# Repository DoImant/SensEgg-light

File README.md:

# SensEgg-Light

This is a circuit board layout for a weather sensor. A BME280 is used to measure temperature, humidity and air pressure. In addition, an NTC ( B+B Sensors TS-NTC-103) is used for temperature measurement, the accuracy of which is significantly better than that of the BME280. The recorded data is sent to a receiver by radio (nrf24 module). 

Power is supplied via a CR2032 3V coin cell. The name comes from the fact that the circuit board fits into a kinder surprise (egg).

The creator of this PCB is @Spaghetticode from arduinoforum.de. I have only implemented his design in KiCad.

## More about the Sensegg-Ligth (in german) 

[https://www.arduinoforum.de/arduino-Thread-SensEgg-light-FunkSensor-ATtiny814-nRF24-BME280-NTC](https://www.arduinoforum.de/arduino-Thread-SensEgg-light-FunkSensor-ATtiny814-nRF24-BME280-NTC)

[SensEgg Firmware](https://github.com/DoImant/Arduino-SensEgg-Light)

## Circuit diagram as PDF file

[Circuit diagram](/SensEgg.pdf)

## The PCB

[Aisler](https://aisler.net/p/TQVCAVJF)

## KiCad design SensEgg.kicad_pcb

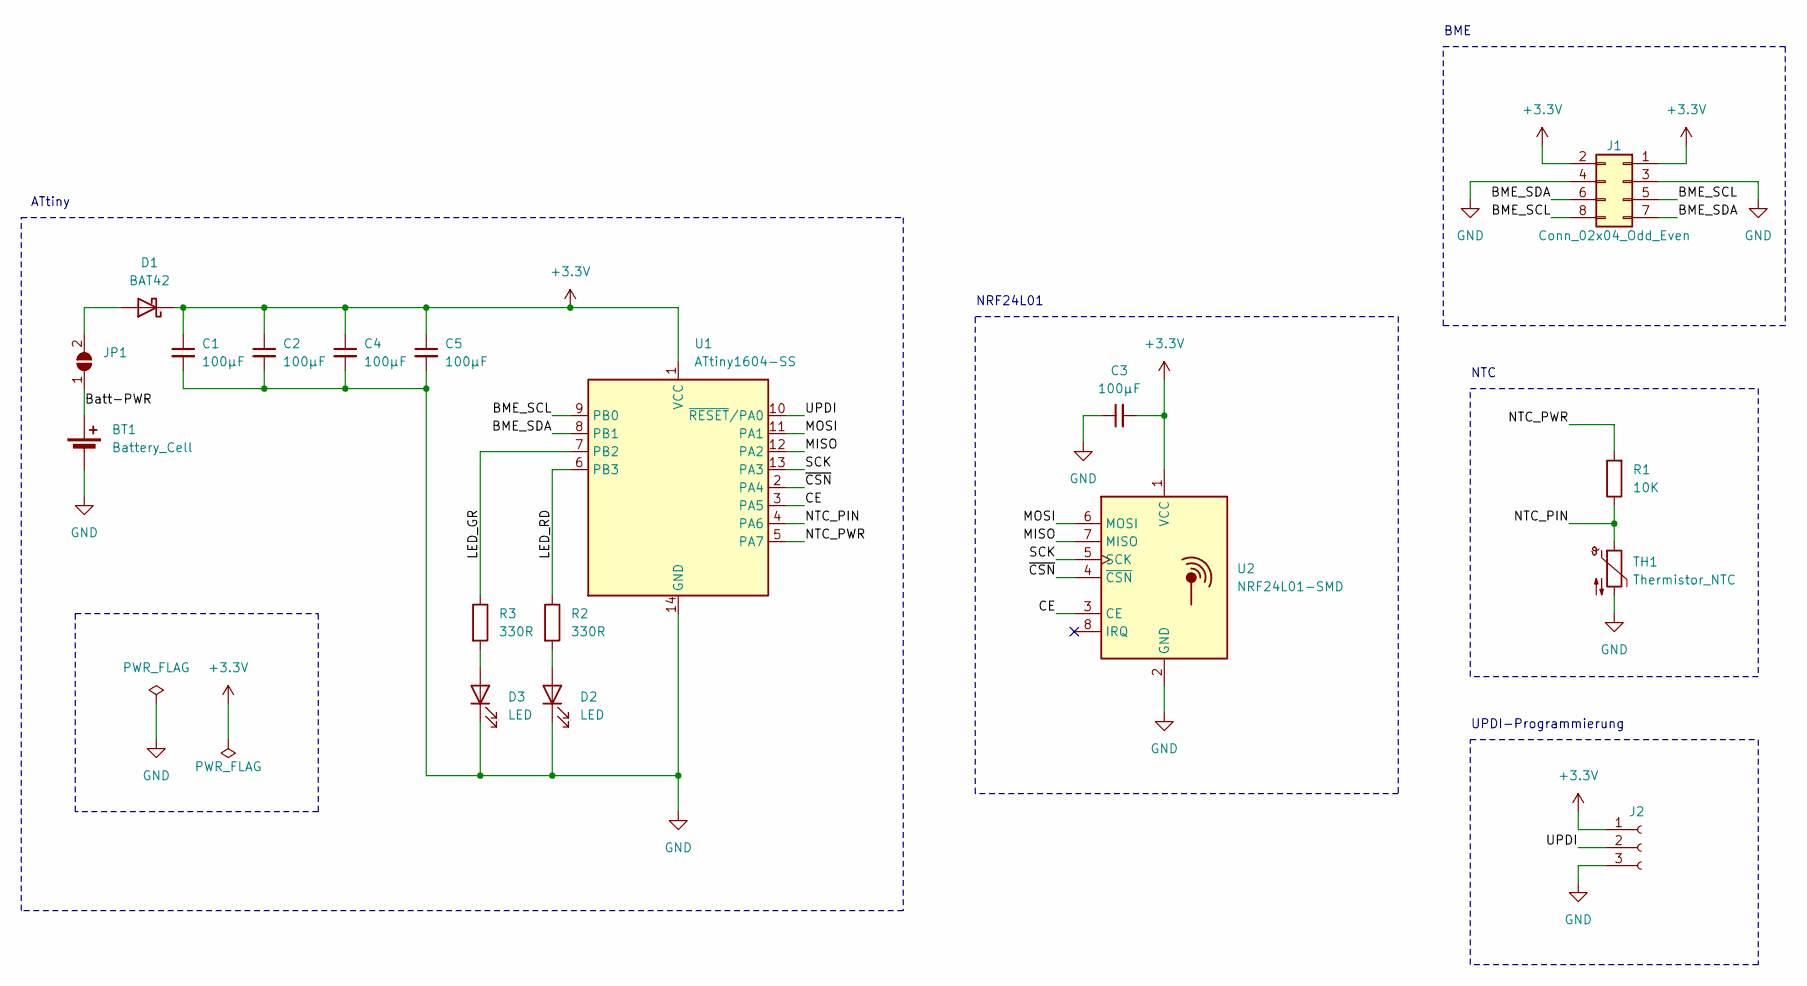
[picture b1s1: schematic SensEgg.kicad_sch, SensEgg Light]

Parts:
BT1: Battery_Cell; China-CR2032
C1, C2, C3, C4, C5: 100µF; C_1206_3216Metric_Pad1.33x1.80mm_HandSolder
D1: BAT42; D_1206_3216Metric_Pad1.42x1.75mm_HandSolder
D2, D3: LED; LED_1206_3216Metric_Pad1.42x1.75mm_HandSolder
J1: Conn_02x04_Odd_Even; PinSocket_2x04_P2.54mm_Vertical
J2: Conn_01x03_Socket; PinHeader_1x03_P2.54mm_Vertical
JP1: SolderJumper_2_Open; SolderJumper-2_P1.3mm_Open_RoundedPad1.0x1.5mm
R1: 10K; R_1206_3216Metric_Pad1.30x1.75mm_HandSolder
R2, R3: 330R; R_1206_3216Metric_Pad1.30x1.75mm_HandSolder
TH1: Thermistor_NTC; TS-NTC-XXX_1x02_P2.54mm
U1: ATtiny1604-SS; SOIC-14_3.9x8.7mm_P1.27mm
U2: NRF24L01-SMD; nRF24L01-SMD

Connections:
+3.3V: C1.1, C2.1, C3.2, C4.1, C5.1, D1.1 (K), J1.1, J1.2, J2.1, U1.1 (VCC), U2.1 (VCC)
/BME_SCL: J1.5, J1.8, U1.9 (PB0)
/BME_SDA: J1.6, J1.7, U1.8 (PB1)
/Batt-PWR: BT1.1 (+), JP1.1 (A)
/CE: U1.3 (PA5), U2.3 (CE)
/LED_GR: R3.1, U1.7 (PB2)
/LED_RD: R2.1, U1.6 (PB3)
/MISO: U1.12 (PA2), U2.7 (MISO)
/MOSI: U1.11 (PA1), U2.6 (MOSI)
/NTC_PIN: R1.1, TH1.1, U1.4 (PA6)
/NTC_PWR: R1.2, U1.5 (PA7)
/SCK: U1.13 (PA3), U2.5 (SCK)
/UPDI: J2.2, U1.10 (~RESET/PA0)
/~CSN: U1.2 (PA4), U2.4 (~CSN)
GND: BT1.2 (-), C1.2, C2.2, C3.1, C4.2, C5.2, D2.1 (K), D3.1 (K), J1.3, J1.4, J2.3, TH1.2, U1.14 (GND), U2.2 (GND)
unnamed: D1.2 (A), JP1.2 (B)
unnamed: D2.2 (A), R2.2
unnamed: D3.2 (A), R3.2

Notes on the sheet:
NRF24L01
BME
NTC
UPDI-Programmierung
ATtiny

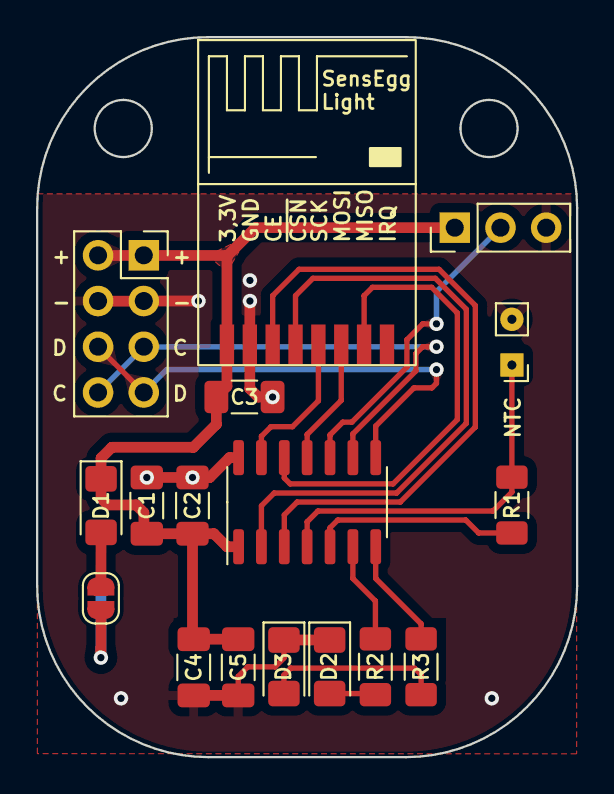
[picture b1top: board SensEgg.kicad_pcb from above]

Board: 2 copper layers, 30.0 x 40.0 mm, 18 parts (1 on the bottom side), 18 nets.

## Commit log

2024-01-05 README changed
